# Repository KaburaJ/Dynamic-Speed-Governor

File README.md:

# DYNAMIC SPEED GOVERNOR FOR HOTSPOT AND SPEED RATED AREAS

---
This repository contains the workflow of a dynamic speed governor. Designed to change as per a location's speed limit, this dynamic speed governor is highly applicable in school zones, hospitals and black spots among others. 

---

## PROBLEM STATEMENT
Overspeeding is among the leading causes of road carnage. Loss of valuable lives as well as destruction of property arise as a result of these accidents. Consequently, the government has erected signposts indicating the speed limit of a certain area. Other measures include the use of traffic lights as well as speed detectors. The project aims to inform  the driver about the zones and the speed limit automatically, which is done by means of using RF technology. The objective of this project is to 
automatically control the speed of the vehicles at speed restricted areas such as schools and hospitals.  

## HOW?
At particular zones (specifically those with existing signposts), transmitters which are tuned at a frequency of about 433MHZ are mounted. These transmitters continuously radiate RF signals. When the vehicle comes within the range of this signal, the receiver (which is mounted on the vehicle) gets activated. Whenever the vehicle is within the zone, the vehicle speed is regulated as per the area's speed limit. This means that the vehicle's speed is decreased to some value which is below the speed limit and kept constant until the vehicle moves out of the zone.

## IMPLEMENTATION
This was done using `Arduino`, `Proteus` and `KiCad` softwares. 

## COMPONENTS USED

### For the transmitter circuit: 

•	`Radio frequency transmitter module` 

This is a small PCB sub-assembly capable of transmitting and modulating a radio wave to carry data.

•	`M145026` or `HT12E` (Encoder)

Converts parallel inputs into serial output. It encodes the 12 bit parallel data into serial for transmission through an RF transmitter. These 12 bit are divided into 8 address bit and 4 data bits.

•	`Push-buttons` 

It is a simple switch mechanism to control the speed limits aspects of the project. The comprise of the 20, 40, 60 and 80 km/hr speed limits.

•   `Two 10k Resistors`

•   `1 uF Capacitor`

### For the receiver cicuit:

•	`Radio frequency receiver module` 

It is a device that accepts radio frequencies from a remote transmitter.

•	`M145027` or `HT12D` (Decoder) 

Used after the RF receiver to decode the serial format and retrieve the original signals as outputs.

•	`Voltage regulator` 

It is system designed to automatically maintain a constant voltage.

•	`Arduino` (Microcontroller) 

•	`Five 200 ohms Resistors` 

•   `Two 10k resistors`

•   ` 1 uF Capacitor`

•	`Push-buttons` 

They include; the `start` button on `pin 12`, `increment`/ `acceleration` button on `pin 4`, `decrement` button on `pin 2`.

•	`Five Leds`

Used to indicate the limit being set in by the remote on the receiver. 

•   `12C` or `LM016` (LCD)

Displays instructions to the vehicle driver

•   `PCF8574`

Used with `LM016`. It has two output pins, making the LCD programming much easier.

•   `L298` (Motor Driver)

•   ` 12V DC Motor`

Used to simulate the behaviour of the vehicle's wheels whilst the program runs.

•   `Buzzer`

Used as an indicator that warns the driver of the changing speed limits - therefore giving him or her an opportunity to decrease the vehicle's speed manually. If ignored, the speed governing system takes over.

## WORKFLOW

## RESULTS
Transmitter PCB results:

Receiver PCB results:

## CONCLUSION

The strategy for this project was to produce a much easily operable and reliable device
This design explains the vehicle speed controller based on the RF technology. It has explained how transmitters installed some roads sections and receivers installed in vehicles can be used to communicate with the each other thereby providing control over the vehicle speed. The design approach was based on a combination of two block units which are the transmitter and the receiver
The results obtained were promising and show that this design can be a potential vehicle speed governor because of its capacity to influence the receiver speed, by giving some expected limits i.e. in the empirical trials, the receiver’s speed was successfully changed as a result of the detection of the signals from the transmitter. This would mean that the design can be more reliable, effective and can be a lasting solution in curbing over speeding in Kenya if fully implemented
The design also worked well for a close range of about 20cm between the transmitter and the receiver because of low transmit power and the value of each speed limit test was then displayed on the LCD display at the receiver side. 
Thus, there can be hope to revolutionize the traffic management and avoid accidents caused due to over speeding in the near future of our country.

## RECOMMENDATIONS
•	Provision of tools that emulate the external real application environment such as a real vehicle for testing the performance of the developed RF based vehicle speed governor

•	Modification may be done on signal processing for digital speed display. The speed controller algorithm developed for this speed governor was based on Pulse Width Modulation (PMW) technique at the receiver end, but other control mechanisms such as fuzzy logic system may also be adopted to give   accurate reasoning, acceptable reasoning and also help to deal with uncertainty in the designing process.

•	Further work can be carried out to study how different frequencies avoid high chances of channel interferences in cases of co-located zones/sections of the roads. The 433MHz technology holds less information and the technology itself is very rudimentary. The 433MHz signals are typically only one-way. This however makes the 433 MHz devices, less reliable. So, further research can be carried out using other technologies like Zig Bee (2.4GHz) or Z-Wave (868.42 MHz) for testing purposes.

•	Instead of the radio frequency we could have used GPS solutions such as Google Maps to reduce hardware costs and increase coverage.

•	Accessibility to components needed to achieve the goals of the project

## REFERENCES
•How a Car Works “How a fuel injection system works”, howacarworks.com, [online] Available, https://www.howacarworks.com/basics/how-a-fuel-injection-system-works 

•Arduino “Get Started with Arduino Uno”, Arduino.cc, [online] Available https://www.arduino.cc/en/Guide/ArduinoUno 

•Robot Platform “Dual H-bridge Motor Driver - L293D IC”, robotplatform.com, [online] Available [https://www.robotplatform.com/howto/L293/motor_driver_1.html 

•Lastminute Engineers “How 433MHz RF Tx-Rx Modules Work & Interface with Arduino”, lastminuteenineers.com, [active] Available, https://lastminuteengineers.com/433mhz-rf-wireless-arduino-tutorial/ 

•RoadSafetyNz “How Do Modern Speed Limiters Work?”, roadsafetynz.org, [online] Available, http://www.roadsafetynz.org/modern-speed-limiters.html

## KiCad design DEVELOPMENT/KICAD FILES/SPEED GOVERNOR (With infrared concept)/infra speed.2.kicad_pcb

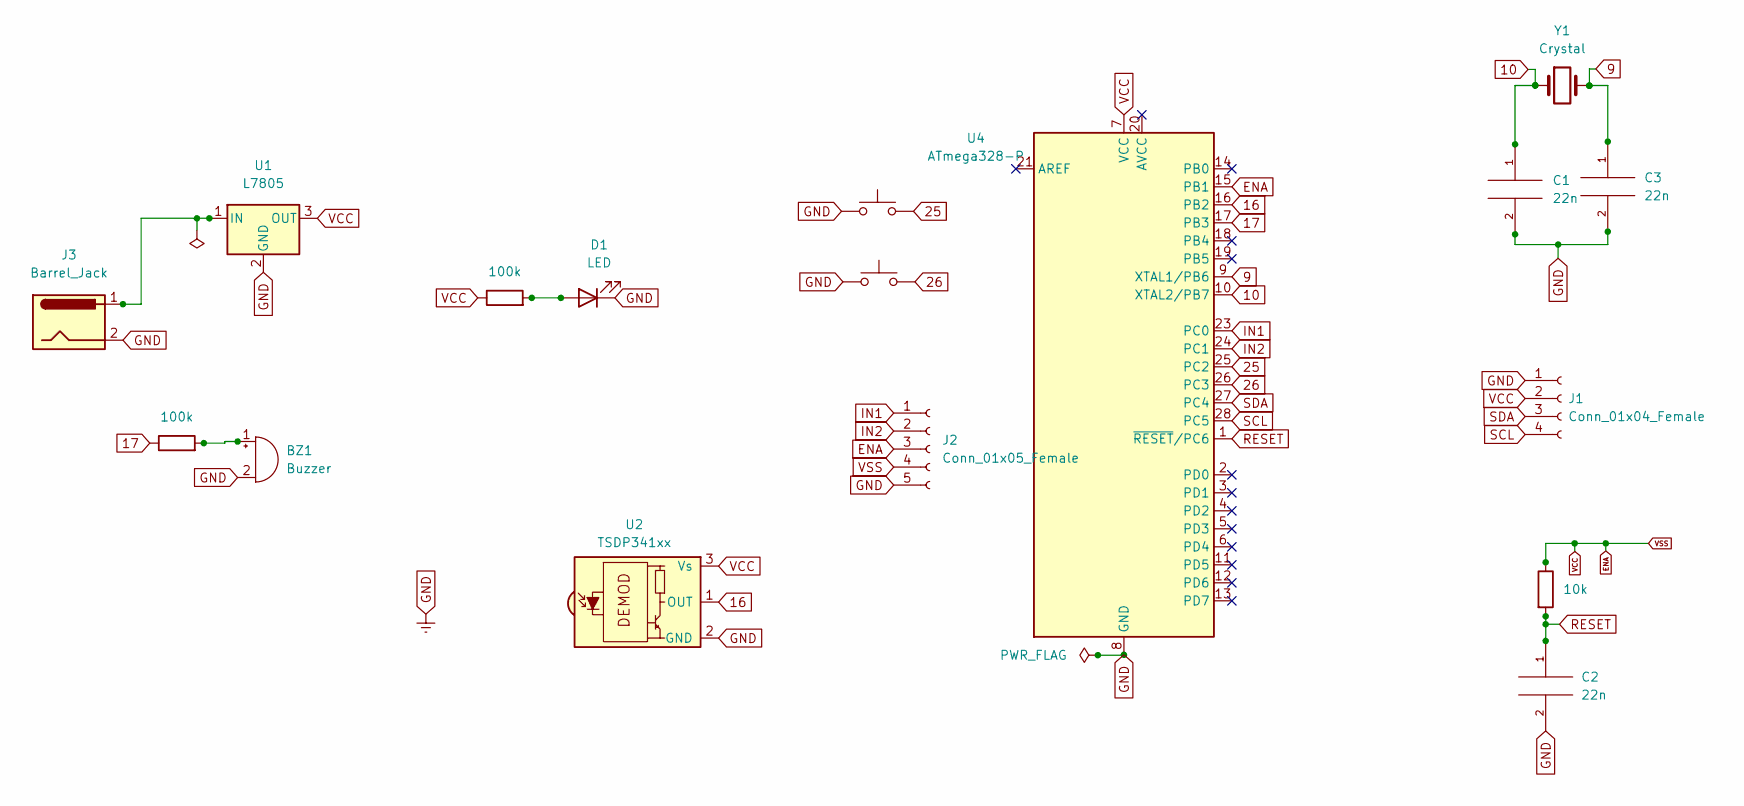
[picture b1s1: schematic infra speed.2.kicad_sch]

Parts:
BZ1: Buzzer; Buzzer_12x9.5RM7.6
C1, C2, C3: 22n; CP_Elec_3x5.4
D1: LED; LED_0805_2012Metric
J1: Conn_01x04_Female; PinSocket_1x04_P2.54mm_Vertical_SMD_Pin1Left
J2: Conn_01x05_Female; PinSocket_1x05_P2.54mm_Vertical
J3: Barrel_Jack; BarrelJack_CUI_PJ-063AH_Horizontal
R1: 10k; R_0201_0603Metric
R2, R3: 100k; R_0201_0603Metric
SW1, SW2: SW_Push; SW_SPST_PTS645
U1: L7805; TO-220F-3_Vertical
U2: TSDP341xx; Vishay_MOLD-3Pin
U4: ATmega328-P; DIP-28_W7.62mm
Y1: Crystal; Crystal_HC52-U_Vertical

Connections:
9: U4.9 (XTAL1/PB6)
10: U4.10 (XTAL2/PB7)
16: U2.1 (OUT), U4.16 (PB2)
17: R2.1, U4.17 (PB3)
25: SW1.2, U4.25 (PC2)
26: SW2.2, U4.26 (PC3)
ENA: J1.2, J2.3, J2.4, R1.1, R3.1, U1.3 (OUT), U2.3 (Vs), U4.7 (VCC), U4.15 (PB1)
GND: BZ1.2 (+), C1.2, C2.2, C3.2, D1.1 (K), J1.1, J2.5, J3.2, SW1.1, SW2.1, U1.2 (GND), U2.2 (GND), U4.8 (GND), U4.22 (GND)
IN1: J2.1, U4.23 (PC0)
IN2: J2.2, U4.24 (PC1)
unnamed: BZ1.1 (-), R2.2
unnamed: C1.1, Y1.1
unnamed: C3.1, Y1.2
unnamed: D1.2 (A), R3.2
unnamed: J3.1, U1.1 (IN)
RESET: C2.1, R1.2, U4.1 (~RESET/PC6)
SCL: J1.4, U4.28 (PC5)
SDA: J1.3, U4.27 (PC4)

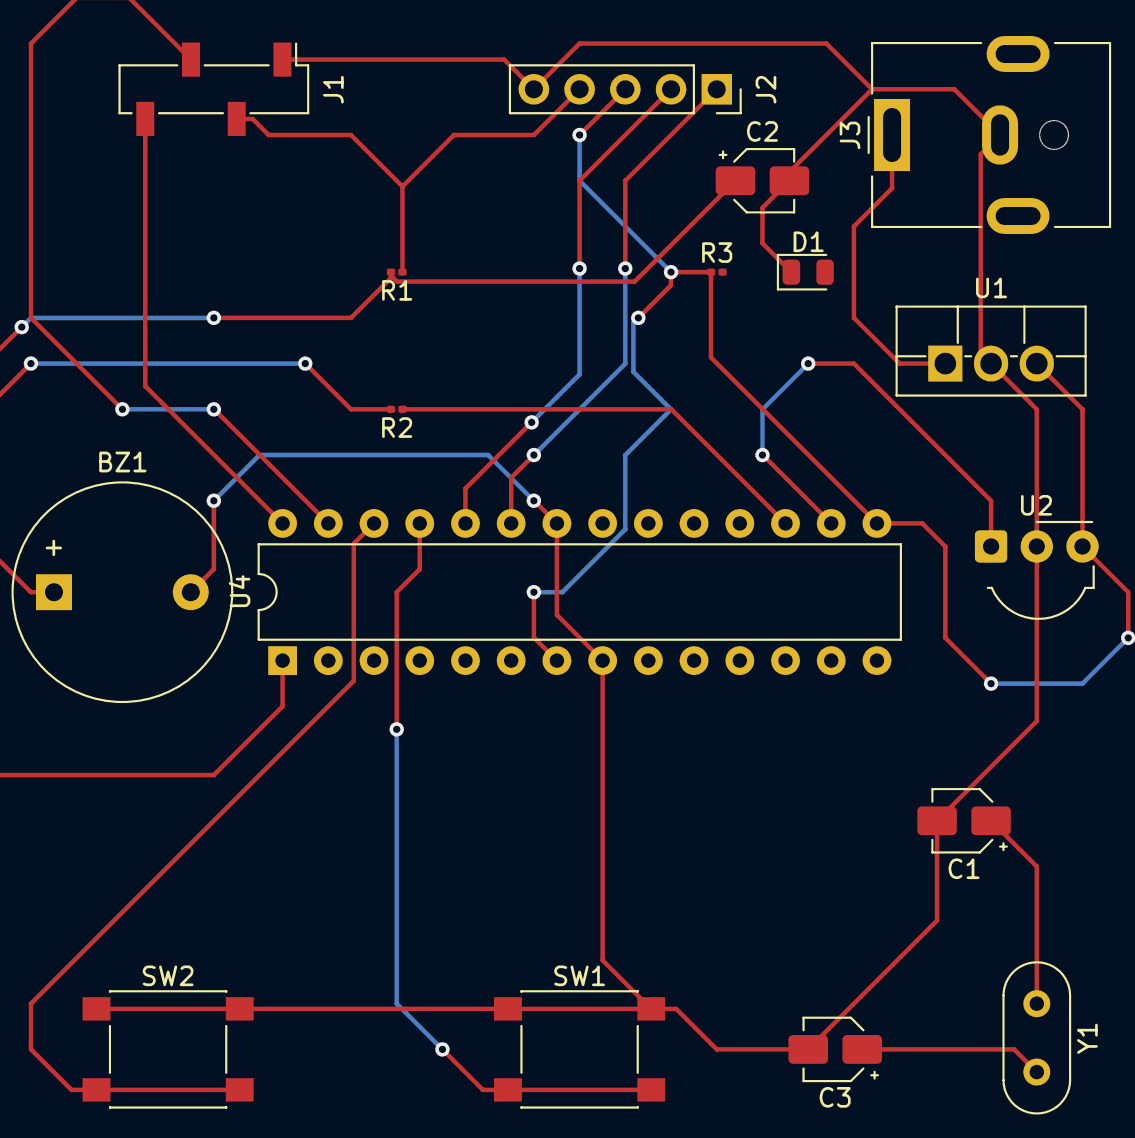
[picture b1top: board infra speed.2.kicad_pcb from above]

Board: 2 copper layers, 17 parts (0 on the bottom side), 16 nets.

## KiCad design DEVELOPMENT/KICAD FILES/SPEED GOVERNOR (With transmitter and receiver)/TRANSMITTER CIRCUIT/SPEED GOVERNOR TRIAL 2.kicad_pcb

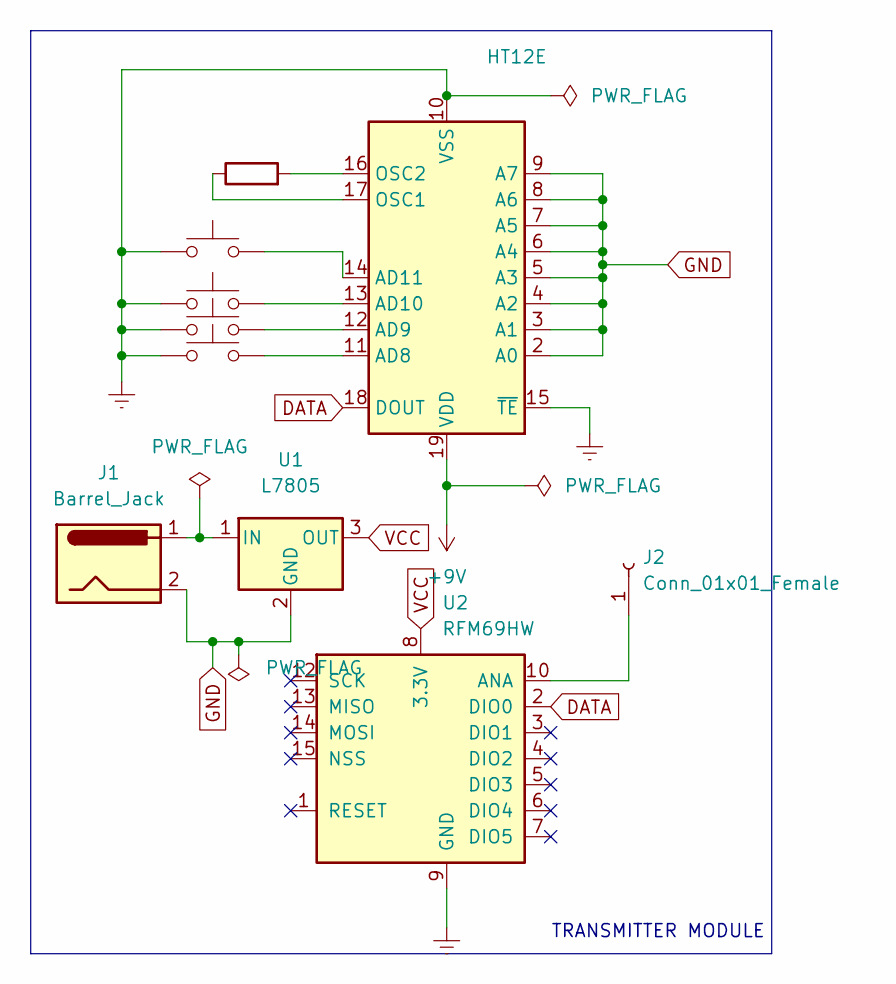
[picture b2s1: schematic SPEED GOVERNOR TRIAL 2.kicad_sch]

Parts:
J1: Barrel_Jack; BarrelJack_CUI_PJ-063AH_Horizontal
J2: Conn_01x01_Female; PinSocket_1x02_P1.00mm_Vertical
R1: 1.1M; R_Axial_DIN0207_L6.3mm_D2.5mm_P10.16mm_Horizontal
SW1, SW2, SW3, SW4: SW_Push; SW_PUSH_6mm
U1: L7805; TO-220-3_Vertical
U2: RFM69HW; HOPERF_RFM69HW
U3: HT12E; SOP-20_7.5x12.8mm_P1.27mm

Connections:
+9V: U3.19 (VDD)
DATA: U2.2 (DIO0), U3.18 (DOUT)
Earth: SW1.1, SW2.1, SW3.1, SW4.1, U2.9 (GND), U2.11 (GND), U3.10 (VSS), U3.15 (~TE)
GND: J1.2, U1.2 (GND), U3.2 (A0), U3.3 (A1), U3.4 (A2), U3.5 (A3), U3.6 (A4), U3.7 (A5), U3.8 (A6), U3.9 (A7)
unnamed: J1.1, U1.1 (IN)
unnamed: J2.1, U2.10 (ANA)
unnamed: R1.1, U3.17 (OSC1)
unnamed: R1.2, U3.16 (OSC2)
unnamed: SW1.2, U3.14 (AD11)
unnamed: SW2.2, U3.13 (AD10)
unnamed: SW3.2, U3.12 (AD9)
unnamed: SW4.2, U3.11 (AD8)
VCC: U1.3 (OUT), U2.8 (3.3V)

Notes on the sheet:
TRANSMITTER MODULE

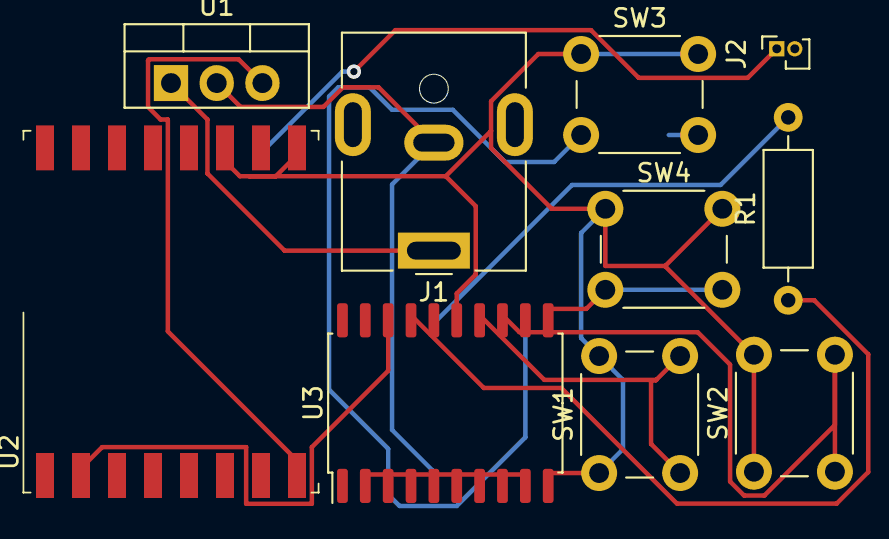
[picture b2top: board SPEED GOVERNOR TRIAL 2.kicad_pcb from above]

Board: 2 copper layers, 10 parts (0 on the bottom side), 12 nets.

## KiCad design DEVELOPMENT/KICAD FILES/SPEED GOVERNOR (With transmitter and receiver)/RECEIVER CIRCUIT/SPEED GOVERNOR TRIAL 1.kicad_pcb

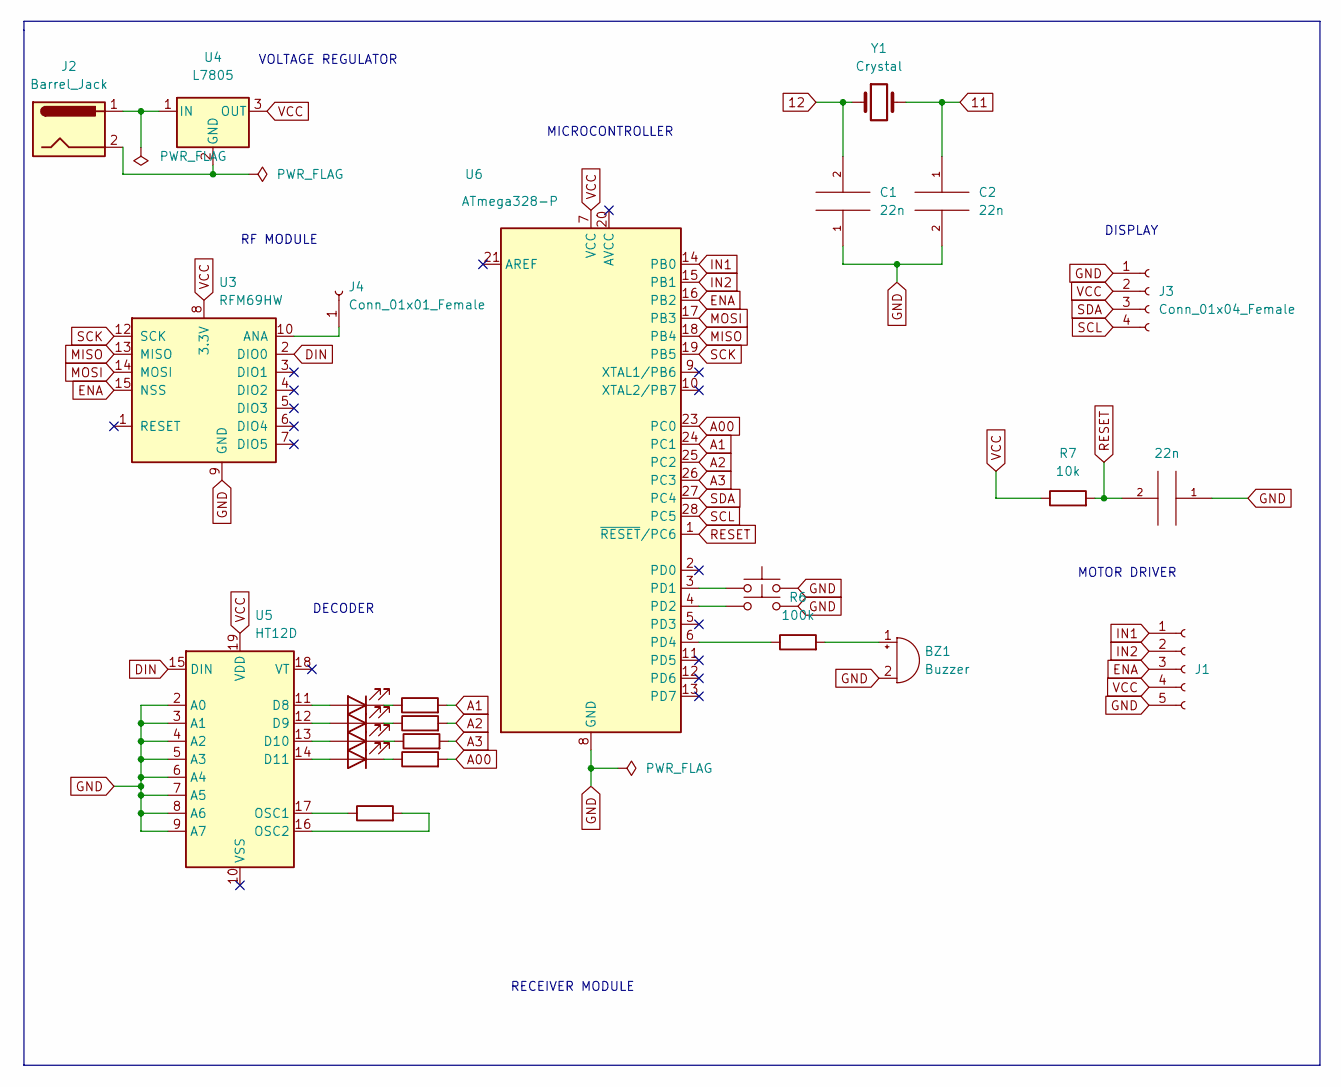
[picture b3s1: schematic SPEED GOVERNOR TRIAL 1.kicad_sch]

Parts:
BZ1: Buzzer; Buzzer_12x9.5RM7.6
C1, C2, C3: 22n; CP_Axial_L10.0mm_D4.5mm_P15.00mm_Horizontal
D1, D2, D3, D4: LED; LED_D5.0mm
J1: Conn_01x05_Female
J2: Barrel_Jack; BarrelJack_CUI_PJ-063AH_Horizontal
J3: Conn_01x04_Female; PinSocket_1x04_P2.54mm_Horizontal
J4: Conn_01x01_Female; PinSocket_1x02_P1.00mm_Vertical
R1: 1.1M; R_Axial_DIN0617_L17.0mm_D6.0mm_P20.32mm_Horizontal
R2, R3, R4, R5, R6: 100k; R_Axial_DIN0617_L17.0mm_D6.0mm_P20.32mm_Horizontal
R7: 10k; R_Axial_DIN0617_L17.0mm_D6.0mm_P20.32mm_Horizontal
SW1, SW2: SW_Push; SW_PUSH_6mm_H4.3mm
U3: RFM69HW; HOPERF_RFM69HW
U4: L7805; TO-220-3_Vertical
U5: HT12D; SOP-20_7.5x12.8mm_P1.27mm
U6: ATmega328-P; DIP-28_W7.62mm
Y1: Crystal; Crystal_HC52-U_Vertical

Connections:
11: C2.1, Y1.2
12: C1.2, Y1.1
A00: R4.2, U6.23 (PC0)
A1: R2.2, U6.24 (PC1)
A2: R3.2, U6.25 (PC2)
A3: R5.2, U6.26 (PC3)
DIN: U3.2 (DIO0), U5.15 (DIN)
ENA: J1.3, U3.15 (NSS), U6.16 (PB2)
GND: BZ1.2 (+), C1.1, C2.2, C3.1, J1.5, J1.6, J1.7, J1.8, J3.1, SW1.2, SW2.2, U3.9 (GND), U3.11 (GND), U5.2 (A0), U5.3 (A1), U5.4 (A2), U5.5 (A3), U5.6 (A4), U5.7 (A5), U5.8 (A6), U5.9 (A7), U6.8 (GND), U6.22 (GND)
IN1: J1.1, U6.14 (PB0)
IN2: J1.2, U6.15 (PB1)
MISO: U3.13 (MISO), U6.18 (PB4)
MOSI: U3.14 (MOSI), U6.17 (PB3)
unnamed: BZ1.1 (-), R6.2
unnamed: D1.1 (K), R2.1
unnamed: D1.2 (A), U5.11 (D8)
unnamed: D2.1 (K), R3.1
unnamed: D2.2 (A), U5.12 (D9)
unnamed: D3.1 (K), R5.1
unnamed: D3.2 (A), U5.13 (D10)
unnamed: D4.1 (K), R4.1
unnamed: D4.2 (A), U5.14 (D11)
unnamed: J2.1, U4.1 (IN)
unnamed: J2.2, U4.2 (GND)
unnamed: J4.1, U3.10 (ANA)
unnamed: R1.1, U5.17 (OSC1)
unnamed: R1.2, U5.16 (OSC2)
unnamed: R6.1, U6.6 (PD4)
unnamed: SW1.1, U6.3 (PD1)
unnamed: SW2.1, U6.4 (PD2)
RESET: C3.2, R7.2, U6.1 (~RESET/PC6)
SCK: U3.12 (SCK), U6.19 (PB5)
SCL: J3.4, U6.28 (PC5)
SDA: J3.3, U6.27 (PC4)
VCC: J1.4, J3.2, R7.1, U3.8 (3.3V), U4.3 (OUT), U5.19 (VDD), U6.7 (VCC)

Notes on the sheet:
VOLTAGE REGULATOR
DISPLAY
RECEIVER MODULE
MICROCONTROLLER
RF MODULE
DECODER
MOTOR DRIVER

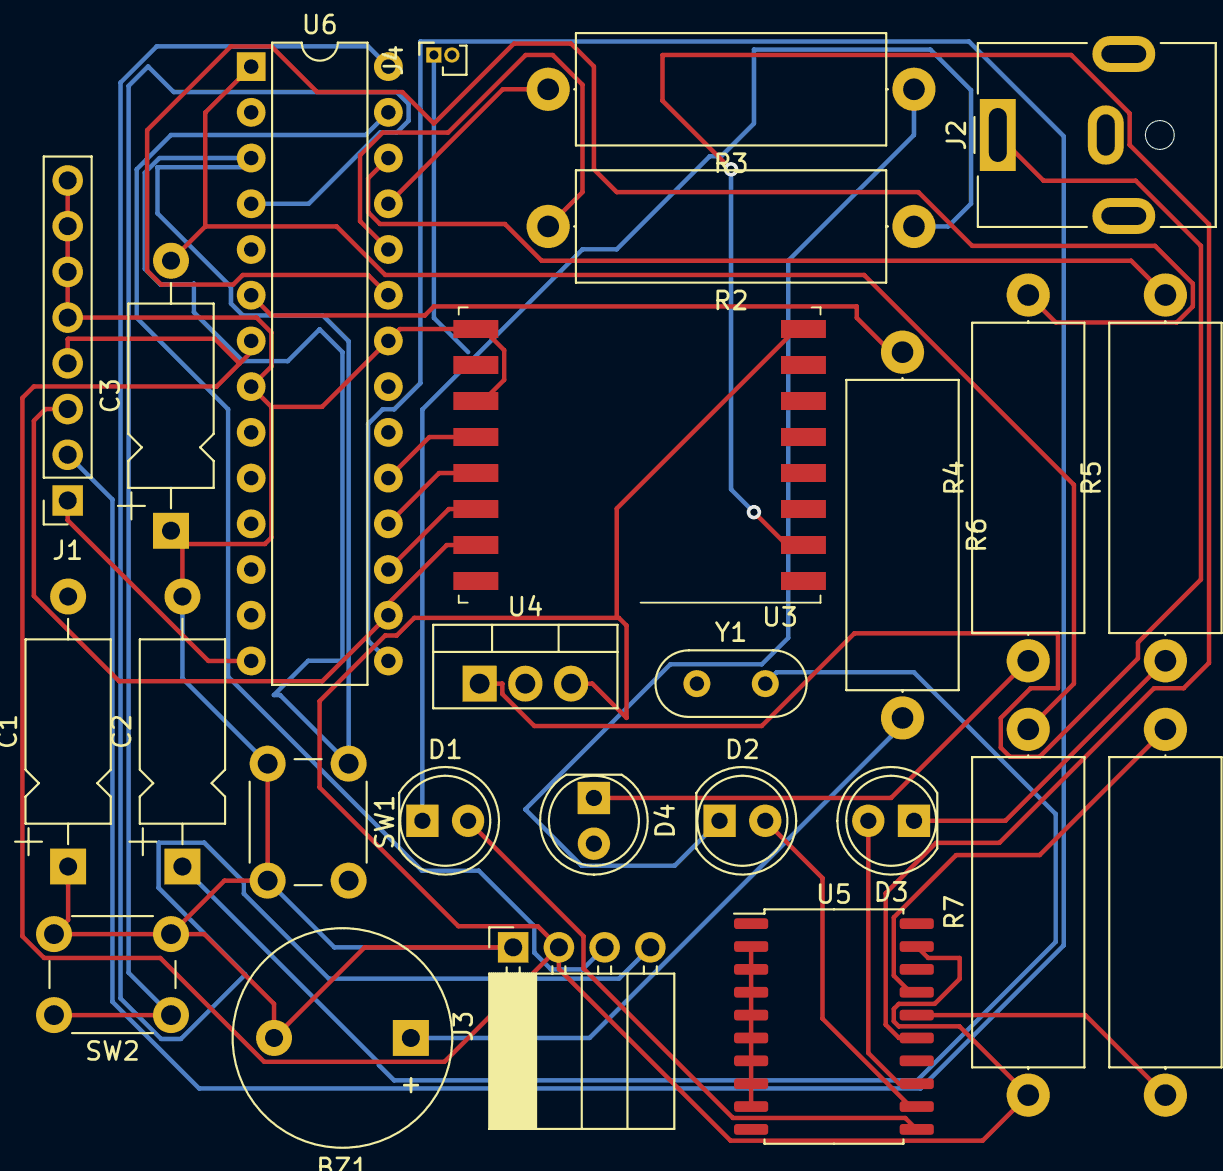
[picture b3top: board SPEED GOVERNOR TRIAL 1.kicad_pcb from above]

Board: 2 copper layers, 26 parts (0 on the bottom side), 35 nets.
